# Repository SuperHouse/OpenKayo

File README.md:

# OpenKayo Kayo-A4 GCode Adapter

Connects to the serial interface of a Kayo-A4 pick-and-place
machine, and provides a USB interface with an onboard GCode 
interpreter that translates messages into the format necessary 
for the Kayo's motion controller.

This allows Kayo machines to be controlled using [OpenPnP](https://openpnp.org/).

## Hardware Requirements

You will need a computer running OpenPnP, with sufficient USB ports 
to handle the connections to the controller, cameras, etc. This 
is a normal OpenPnP requirement so check the OpenPnP docs for 
details.

The hardware adapter portion of the project can minimally be built with an
ESP8266-based dev board such as a Wemos D1 Mini and some cables.

A dedicated ESP32-S3 hardware design is provided, which includes
additional features such as a CAN bus interface to integrate with other
devices on the production line.

**Adapter Board Features**

 * USB-C socket for connection to host computer running OpenPnP
 * ESP32-S3 MCU
 * 3-way 3.81mm screw socket for connection to Kayo serial cable
 * Onboard USB hub with 2 spare ports exposed
 * RGB LED for status display
 * Connections for external RGB LED strip for traffic-light status display etc
 * 128x32 OLED
 * Piezo for alarms
 * CAN bus interface with optional CAN termination
 * Can be powered via USB if only a serial connection + USB is required
 * Can be powered at 12V via screw terminals to pass power on to CAN bus
 * Can be powered at 12V via CAN bus if another device on the bus is powered

## Serial Connection

Kayo machines are supplied with a Windows PC running their proprietary 
control software, which is connected to a motion 
controller mounted inside the chassis via a serial connection. The
serial port is connected using a 3-way 3.81mm pitch pluggable screw 
terminal, which includes signal GND, TX, and RX:

 * Logic voltage: 3.3V
 * 115200 8N1

## Axis Configuration

The protocol converter uses the axes listed below. OpenPnP needs to be 
configured to use these same axes.

 * X: horizontal left/right
 * Y: horizontal forward/back
 * Z: virtual vertical axis for top camera, which doesn't physically move vertically
 * A, B, C, D: rotational axes for nozzles 1-4
 * I, J, K, L: z (vertical) axes for nozzles 1-4

Kayo "home" is in the top right corner at coordinates "0,0", so the 
working area is negative coordinates relative to that. That may sound 
confusing at first but it works out quite nicely in practice. For example, 
a typical board origin when clamped on the conveyor could be at something 
like "-155, -453".

Nozzles are at a 0 position when fully retracted (raised) and typically 
descend to approximately -9.8mm to -10.1mm to touch the surface of a clamped 
PCB or feeder pickup location.

## Supported G-Codes

### Basic movement

| Code             | Meaning                                                                                              |
|------------------|------------------------------------------------------------------------------------------------------|
| G28              | Reset and home                                                                                       |
| G0 X*pos* Y*pos* | Move X & Y to the defined absolute position in mm, eg: "G0 X-23.4 Y-18"                              |
| G0 I*pos*        | Move specified nozzle vertically to absolute position in mm, eg: "G0 I-7.6" to send nozzle 1 to -7.6mm (I=n1, J=n2, K=n3, L=n4) |       
| G0 A*pos*        | Rotate specified nozzle to an absolute angle in degrees, eg: "G0 A48" to send nozzle 1 to an angle of 48 degrees (A=n1, B=n2, C=n3, D=n4)      |

**Note:** the Kayo motion controller has an interlock on X/Y movement with Z 
axis displacement. You CANNOT move the machine in X or Y axis while holding 
a nozzle partly extended. It handles this by automatically retracting all 
nozzles whenever it gets an X/Y movement command.

This means that you can't use advanced motion planning in OpenPnP, and you 
also can't assume that you know the Z axis position of any nozzle. If you 
move the head in X/Y, all Z axes will be immediately zeroed with no warning.

### Vac / Blow
| Code             | Meaning                                                                                              |
|------------------|------------------------------------------------------------------------------------------------------|
| M2 N*noz*        | Close vac and open blow on specified nozzle, eg: "M2 N2"                                             |
| M3               | Close vac and blow on all nozzles                                                                    |
| M4 N*noz*        | Open blow on selected nozzle, eg: "M4 N3"                                                            |
| M5 N*noz*        | Close blow on selected nozzle, eg: "M5 N2"                                                           |
| M6 N*noz*        | Open vac on selected nozzle, eg: "M6 N1"                                                             |
| M7 N*noz*        | Close vac on selected nozzle, eg: "M7 N1"                                                            |

### Conveyor Belt
| Code             | Meaning                                                                                              |
|------------------|------------------------------------------------------------------------------------------------------|
| M2               | Reset conveyor                                                                                       |
| M21 N*width*     | Adjust conveyor to specified width + configured margin, eg: "M21 N93.4"                              |
| M22              | Ingest a PCB and clamp it in position                                                                |
| M23              | Unclamp PCB and move it to the exit location                                                         |
| M24              | Start conveyor                                                                                       |
| M25              | Stop conveyor and drop pin                                                                           |
| M26              | Engages the stop pin                                                                                 |
| M27              | Clamp a PCB on the conveyor                                                                          |

### Lights
| Code              | Meaning                                                                                             |
|-------------------|-----------------------------------------------------------------------------------------------------|
| M30               | Turn off camera lights                                                                              |
| M31 S*brightness* | Turn on fast camera light at specified brightness %, eg: "M31 S15"                                 |
| M32 S*brightness* | Turn on precision camera light at specified brightness %, eg: "M32 S46"                             |

### Status
| Code             | Meaning                                                                                              |
|------------------|------------------------------------------------------------------------------------------------------|
| M114             | Report position                                                                                      |
| M115             | Report firmware type and version                                                                     |

### Feeders
| Code             | Meaning                                                                                              |
|------------------|------------------------------------------------------------------------------------------------------|
| M600 N*feeder*   | Open specified feeder, eg: "M600 N12"                                                                |
| M601             | Close feeders (no need to specify)                                                                   |

**Note:** The Kayo motion controller only ever allows a single feeder to be open 
at a time. If you have one feeder open and then send an open command for a different 
feeder, the first one will be closed automatically.

There is no command to close a specific feeder. M601 closes whatever was last opened.

### Diagnostic
| Code               | Meaning                                                                                            |
|--------------------|----------------------------------------------------------------------------------------------------|
|M99 N*noz* S*steps* | Send microsteps to specified nozzle rotation stepper, eg: "M99 N1 S1234"                           |

## Camera Modifications

### Bottom Cameras

I have been unable to connect the 5 factory bottom cameras (1 x precision 
camera and a 4-way high-speed camera array) to OpenPnP on either 
Ubuntu or MacOS. You may have more success on Windows: please let me know!

On my machines I have unscrewed the 4-way camera array and tucked it away 
under the feeder manifold, and also removed the precision camera. I replaced 
that with an ELP Mini 720p OV9712 USB industrial camera with a 6mm lens, 
using a 3D-printed camera mount and a lens spacer to change the focal length.

This particular camera is very commonly used for OpenPnP so it's a 
well-known and well-supported device.

**1. Remove light bracket and the original camera:**

**2. 3D-print mounting plate and lens spacer:**

**3. Remove lens from ELP camera:**

**4. Reattach lens with 6mm M2 bolts with spacer:**

**5. Attach mounting plate with M3 bolts:**

**6. Pass cable through mounting plate and screw camera on with 2mm self tappers:**

Finally, reinstall the light bracket and then do the usual focus and 
camera calibration process in OpenPnP.

### Top Camera

The top camera has an analog output. I connected it to an analog-to-HDMI 
converter, which then goes to a cheap HDMI-to-USB converter so that it 
appears as a webcam under Linux and can be accessed by OpenPnP.

## Discard Tray

You can use the original discard tray behind the PCB area, but with 
the 4-camera array removed there is an ideal location for a discard 
tray right behind the camera location. This allows a very short movement 
to the tray if the vision pipeline rejects the parts.

I have designed a discard tray holder that has a 1x2 Gridfinity mount 
in the base, and holes to attach it to the T-slot front rail using 
T-nuts and M3 bolts:

You can use a regular 1x2 Gridfinity tray. I've included a design for 
a 1x1 tray with the height set to match the mounting rail. OpenPnP 
currently only supports a single discard location, but support for 
multiple trays is in development:

## Kayo Protocol

The control protocol for the Kayo motion controller uses 8-byte 
messages in both directions, with no terminator. Message boundaries 
are discovered by watching for a leading character, tracking the 
number of bytes received, and timing out as a fallback to handle 
incomplete messages or errors.

The protocol is embodied in the source code. Docs to be added here 
later.

## Hardware

The "Hardware" directory contains the PCB design as an EAGLE project. 
This can be imported into KiCAD, or opened natively using Fusion360.

## Firmware

The "Firmware" directory contains example firmware as an Arduino
project. The full Arduino IDE board settings are in the header comment
of `OpenKayo.ino`.

**Important:** set Tools -> USB Mode to "USB-OTG (TinyUSB)", not
"Hardware CDC and JTAG". In Hardware CDC mode (tested with esp32 core
2.0.7), a reply whose last USB packet is exactly 64 bytes is held by
Linux hosts until the board sends more data. OpenPnP then times out
waiting for "ok", and its command confirmations get out of step.

The firmware sends exactly one response for each G-code line: "ok" when
the command has finished, or a single line starting with "ERR:" if it
failed. A command fails if the Kayo doesn't reply within the timeouts set
in `config.h`: 5 seconds for most commands, and 60 seconds for homing and
conveyor commands. In OpenPnP's GcodeDriver settings:

 * "Command Error Regex" should match `^ERR:.*`, so that a failed command
   stops the job straight away.
 * "Command Timeout [ms]" must be longer than the firmware's longest
   timeout, for example 65000. If OpenPnP gives up first, its command
   confirmations get out of step.

## Credits

 * Jonathan Oxer <jon@oxer.com.au>

Heavily inspired by Glen English's Python-based UI for the Kayo, in
particular his work decoding the message format used by the factory
software.

## License

Copyright 2022-2025 SuperHouse Automation Pty Ltd  www.superhouse.tv  

The hardware portion of this project is licensed under the TAPR Open
Hardware License (www.tapr.org/OHL). The "license" folder within this
repository contains a copy of this license in plain text format.

The software portion of this project is licensed under the Simplified
BSD License. The "licence" folder within this project contains a
copy of this license in plain text format.

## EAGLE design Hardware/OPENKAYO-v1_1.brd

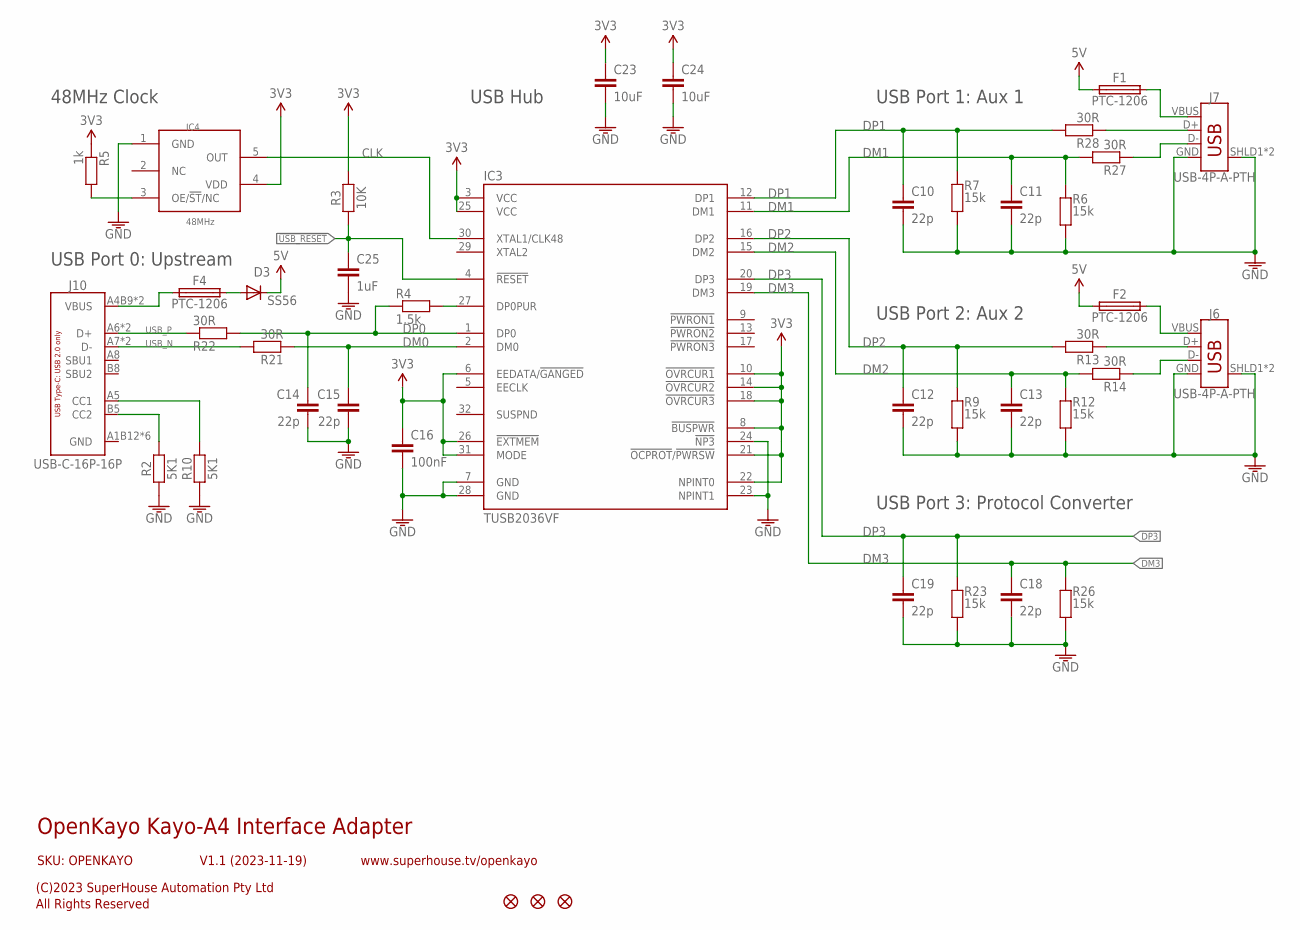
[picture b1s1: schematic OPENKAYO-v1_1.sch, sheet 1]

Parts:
C10, C11, C12, C13, C14, C15, C18, C19: 22p; C0603
C16: 100nF; C0603
C23, C24: 10uF; C0805
C25: 1uF; C0603
D3: SS56; SMA-DIODE
F1, F2, F4: PTC-1206; 1206
FID1, FID2, FID3: FIDUCIAL1X2.5; FIDUCIAL-1X2.5
IC3: TUSB2036VF; PQFP-G32
IC4: 48MHz; SOT-23-5
J6, J7: USB-4P-A-PTH; USB-A-PTH
J10: USB-C-16P-16P; USB-C-16P
R2, R10: 5K1; R0603
R3: 10K; R0603
R4: 1.5k; R0603
R5: 1k; R0603
R6, R7, R9, R12, R23, R26: 15k; R0603
R13, R14, R21, R22, R27, R28: 30R; R0603

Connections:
3.3V: C16.1, C23.1, C24.1, IC3.3 (VCC), IC3.6 (EEDATA/!GANGED), IC3.8 (!BUSPWR), IC3.10 (!OVRCUR1), IC3.14 (!OVRCUR2), IC3.18 (!OVRCUR3), IC3.21 (!OCPROT!/!PWRSW!), IC3.22 (NPINT0), IC3.25 (VCC), IC3.26 (!EXTMEM), IC3.31 (MODE), IC4.4 (VDD), R3.2, R5.1; also elsewhere on the board
5V: D3.C, F1.1, F2.1; also elsewhere on the board
!USB_RESET: C25.1, IC3.4 (!RESET), R3.1
CLK: IC3.30 (XTAL1/CLK48), IC4.5 (OUT)
DM0: C15.1, IC3.2 (DM0), R21.2
DM1: C11.1, IC3.11 (DM1), R6.1, R27.2
DM2: C13.1, IC3.15 (DM2), R12.1, R14.2
DM3: C18.1, IC3.19 (DM3), R26.1; also elsewhere on the board
DP0: C14.1, IC3.1 (DP0), R4.1, R22.2
DP1: C10.1, IC3.12 (DP1), R7.1, R28.2
DP2: C12.1, IC3.16 (DP2), R9.1, R13.2
DP3: C19.1, IC3.20 (DP3), R23.1; also elsewhere on the board
GND: C10.2, C11.2, C12.2, C13.2, C14.2, C15.2, C16.2, C18.2, C19.2, C23.2, C24.2, C25.2, IC3.7 (GND), IC3.23 (NPINT1), IC3.24 (!NP3), IC3.28 (GND), IC4.1 (GND), J6.GND, J6.SHLD1 (SHIELD), J6.SHLD2 (SHIELD), J7.GND, J7.SHLD1 (SHIELD), J7.SHLD2 (SHIELD), J10.A1B12 (GND), J10.A12B1 (GND), J10.FIX1 (GND), J10.FIX2 (GND), J10.FIX3 (GND), J10.FIX4 (GND), R2.1, R6.2, R7.2, R9.2, R10.1, R12.2, R23.2, R26.2; also elsewhere on the board
unnamed: IC3.27 (DP0PUR), R4.2
unnamed: IC4.3 (OE/!ST!/NC), R5.2
unnamed: F1.2, J7.VBUS
unnamed: F2.2, J6.VBUS
unnamed: J10.B5 (CC2), R2.2
unnamed: J10.A5 (CC1), R10.2
unnamed: J6.D+, R13.1
unnamed: J6.D-, R14.1
unnamed: J7.D+, R28.1
unnamed: J7.D-, R27.1
unnamed: F4.1, J10.A4B9 (VBUS), J10.A9B4 (VBUS)
unnamed: D3.A, F4.2
USB_N: J10.A7 (D-), J10.B7 (D-), R21.1
USB_P: J10.A6 (D+), J10.B6 (D+), R22.1

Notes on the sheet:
OpenKayo Kayo-A4 Interface Adapter
V1.1 (2023-11-19)
SKU: OPENKAYO
(C)2023 SuperHouse Automation Pty Ltd
All Rights Reserved
www.superhouse.tv/openkayo
USB Port 1: Aux 1
USB Port 2: Aux 2
USB Port 3: Protocol Converter
USB Hub
USB Port 0: Upstream
48MHz Clock

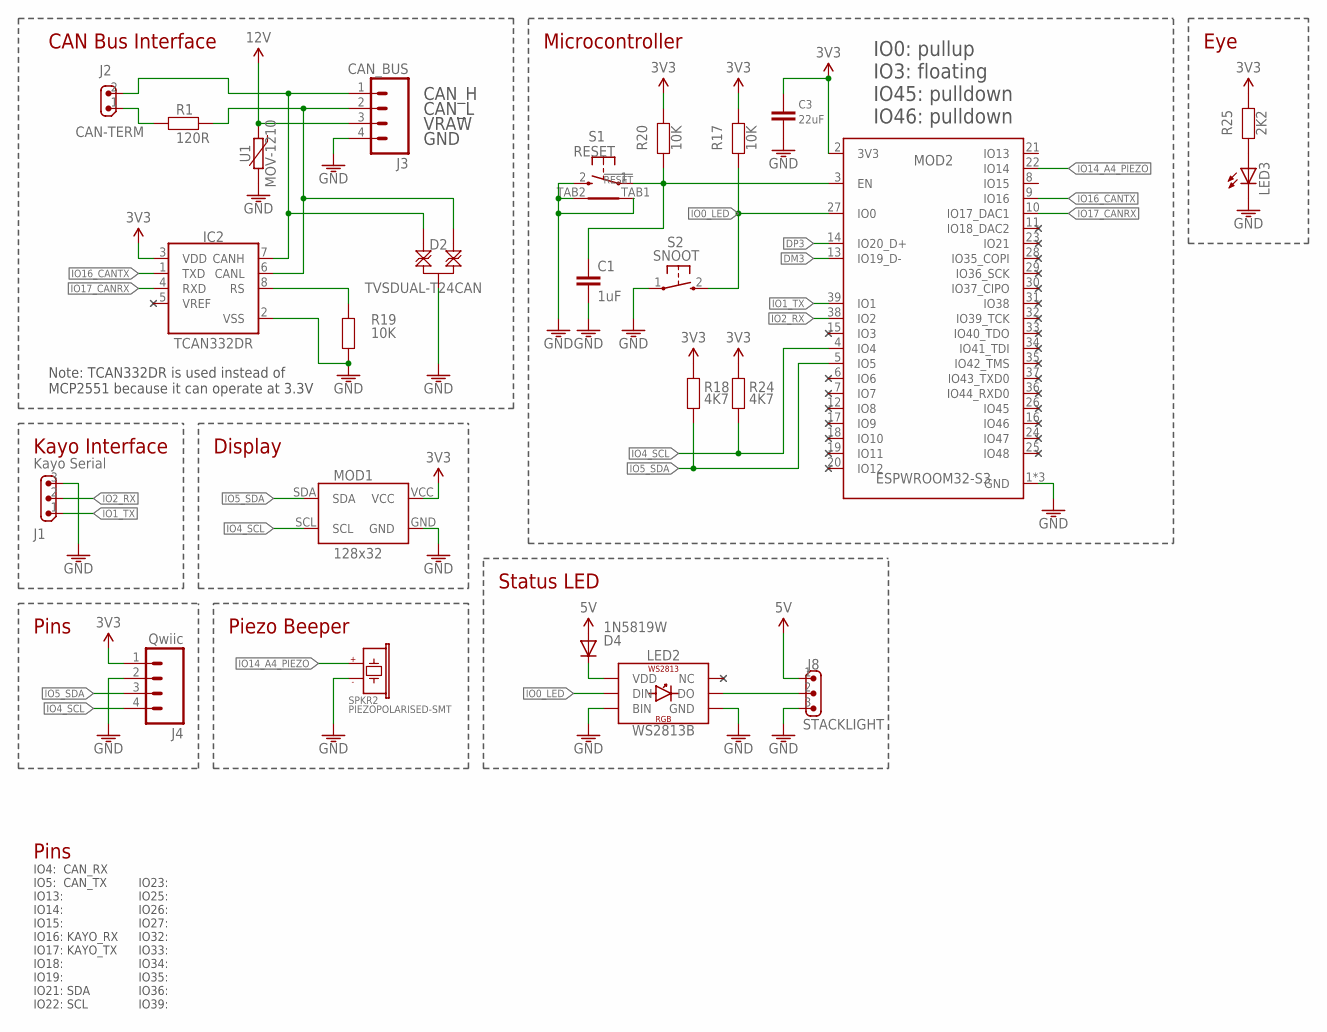
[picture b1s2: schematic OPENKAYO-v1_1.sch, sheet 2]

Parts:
C1: 1uF; C0603
C3: 22uF; C0805
D2: TVSDUAL-T24CAN; SOT23-3
D4: 1N5819W; SOD-123
IC2: TCAN332DR; SOIC8
J1: Kayo Serial; SCREWTERMINAL-3.81MM-HOR-3
J2: CAN-TERM; 1X02-P-JUMP-Y
J3: CAN_BUS; SCREWTERMINAL-3.81MM-HOR-4
J4: Qwiic; JST-SM4B-SH
J8: STACKLIGHT; 1X03
LED2: WS2813B; WS2813
LED3: LED0603; LED-0603
MOD1: 128x32; OLED-128X32-0.91-HEADER
MOD2: ESPWROOM32-S3
R1: 120R; R2010
R17, R19, R20: 10K; R0603
R18, R24: 4K7; R0603
R25: 2K2; R0603
S1: RESET; TYCO-FSMRAJ
S2: SNOOT; TACTILE_SMT_3X4X2
SPKR2: PIEZOPOLARISED-SMT; PIEZO-9.6X9.6-SMT
U1: MOV-1210; 1210

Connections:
3.3V: C3.1, IC2.3 (VDD), J4.1, MOD1.VCC, MOD2.2 (3V3), R17.1, R18.1, R20.1, R24.1, R25.1; also elsewhere on the board
5V: D4.2 (A), J8.1; also elsewhere on the board
12V: J3.3, U1.2; also elsewhere on the board
!RESET: C1.1, MOD2.3 (EN), R20.2, S1.1
CAN_H: D2.2, IC2.7 (CANH), J2.2, J3.1
CAN_L: D2.1, IC2.6 (CANL), J3.2, R1.2
DM3: MOD2.13 (IO19_D-); also elsewhere on the board
DP3: MOD2.14 (IO20_D+); also elsewhere on the board
GND: C1.2, C3.2, D2.3, IC2.2 (VSS), J1.3, J3.4, J4.2, J8.3, LED2.5 (GND), LED2.6 (BIN), LED3.C, MOD1.GND, MOD2.1 (GND), MOD2.40 (GND), MOD2.41 (GND), R19.1, S1.2, S1.TAB1, S1.TAB2, S2.1, SPKR2.2 (-), U1.1; also elsewhere on the board
IO0_LED: LED2.4 (DIN), MOD2.27 (IO0), R17.2, S2.2 (S)
IO1_TX: J1.1, MOD2.39 (IO1)
IO2_RX: J1.2, MOD2.38 (IO2)
IO4_SCL: J4.4, MOD1.SCL, MOD2.4 (IO4), R24.2
IO5_SDA: J4.3, MOD1.SDA, MOD2.5 (IO5), R18.2
IO14_A4_PIEZO: MOD2.22 (IO14), SPKR2.1 (+)
IO16_CANTX: IC2.1 (TXD), MOD2.9 (IO16)
IO17_CANRX: IC2.4 (RXD), MOD2.10 (IO17_DAC1)
IO46: MOD2.16 (IO46)
unnamed: IC2.8 (RS), R19.2
unnamed: LED3.A, R25.2
unnamed: J2.1, R1.1
unnamed: D4.1 (C), LED2.2 (VDD)
unnamed: J8.2, LED2.3 (DO)
NC: LED2.1 (NC)

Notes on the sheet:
CAN Bus Interface
Note: TCAN332DR is used instead of MCP2551 because it can operate at 3.3V
CAN_H
CAN_L
GND
VRAW
Kayo Interface
Piezo Beeper
IO4: CAN_RX IO5: CAN_TX IO13: IO14: IO15: IO16: KAYO_RX IO17: KAYO_TX IO18: IO19: IO21: SDA IO22: SCL
Pins
IO23: IO25: IO26: IO27: IO32: IO33: IO34: IO35: IO36: IO39:
Microcontroller
Display
Status LED
IO0: pullup IO3: floating IO45: pulldown IO46: pulldown
Eye

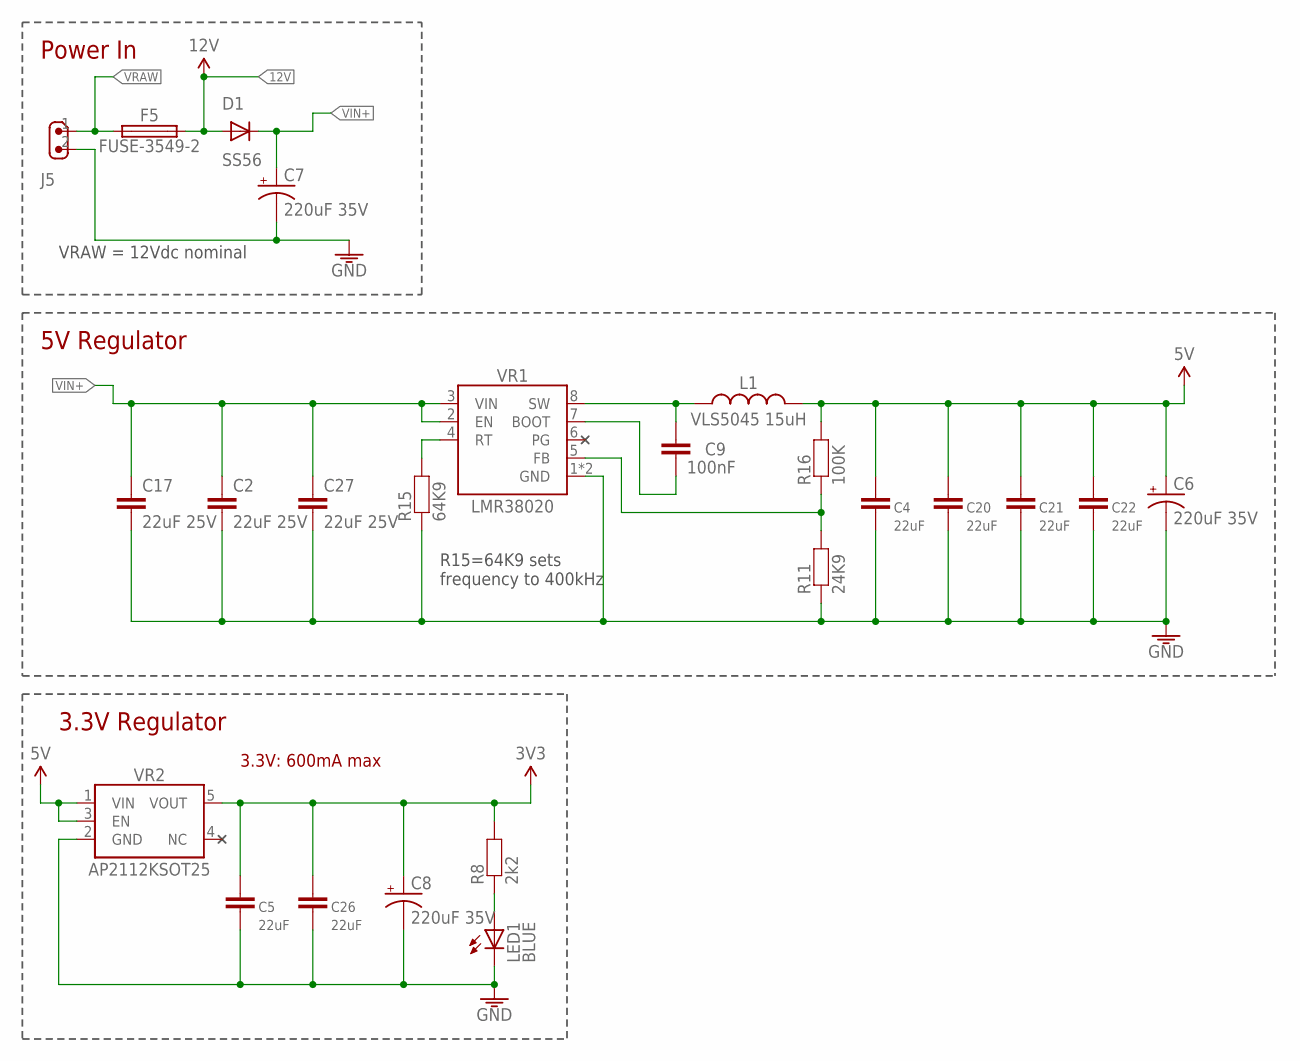
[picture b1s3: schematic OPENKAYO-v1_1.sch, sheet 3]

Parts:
C2, C17, C27: 22uF 25V; C0805
C4, C5, C20, C21, C22, C26: 22uF; C0805
C6, C7, C8: 220uF 35V; PANASONIC_G
C9: 100nF; C0603
D1: SS56; SMA-DIODE
F5: FUSE-3549-2; KS-3549-2
J5: M02-SCREW-3.81MM-HOR; SCREWTERMINAL-3.81MM-HOR-2
L1: VLS5045 15uH; INDUCTOR-5045
LED1: BLUE; LED-0603
R8: 2k2; R0603
R11: 24K9; R0603
R15: 64K9; R0603
R16: 100K; R0603
VR1: LMR38020; HSOIC8
VR2: AP2112KSOT25; SOT23-5

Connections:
3.3V: C5.1, C8.+, C26.1, R8.2, VR2.5 (VOUT); also elsewhere on the board
5V: C4.1, C6.+, C20.1, C21.1, C22.1, L1.2, R16.2, VR2.1 (VIN), VR2.3 (EN); also elsewhere on the board
12V: D1.A, F5.3 (2), F5.4 (2); also elsewhere on the board
GND: C2.2, C4.2, C5.2, C6.-, C7.-, C8.-, C17.2, C20.2, C21.2, C22.2, C26.2, C27.2, J5.2, LED1.C, R11.1, R15.1, VR1.1 (GND), VR1.TGND (GND), VR2.2 (GND); also elsewhere on the board
unnamed: C9.1, L1.1, VR1.8 (SW)
unnamed: R15.2, VR1.4 (RT)
unnamed: R11.2, R16.1, VR1.5 (FB)
unnamed: C9.2, VR1.7 (BOOT)
unnamed: LED1.A, R8.1
PG: VR1.6 (PG)
VIN+: C2.1, C7.+, C17.1, C27.1, D1.C, VR1.2 (EN), VR1.3 (VIN)
VRAW: F5.1, F5.2 (1), J5.1

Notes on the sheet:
3.3V: 600mA max
VRAW = 12Vdc nominal
5V Regulator
3.3V Regulator
Power In
R15=64K9 sets frequency to 400kHz

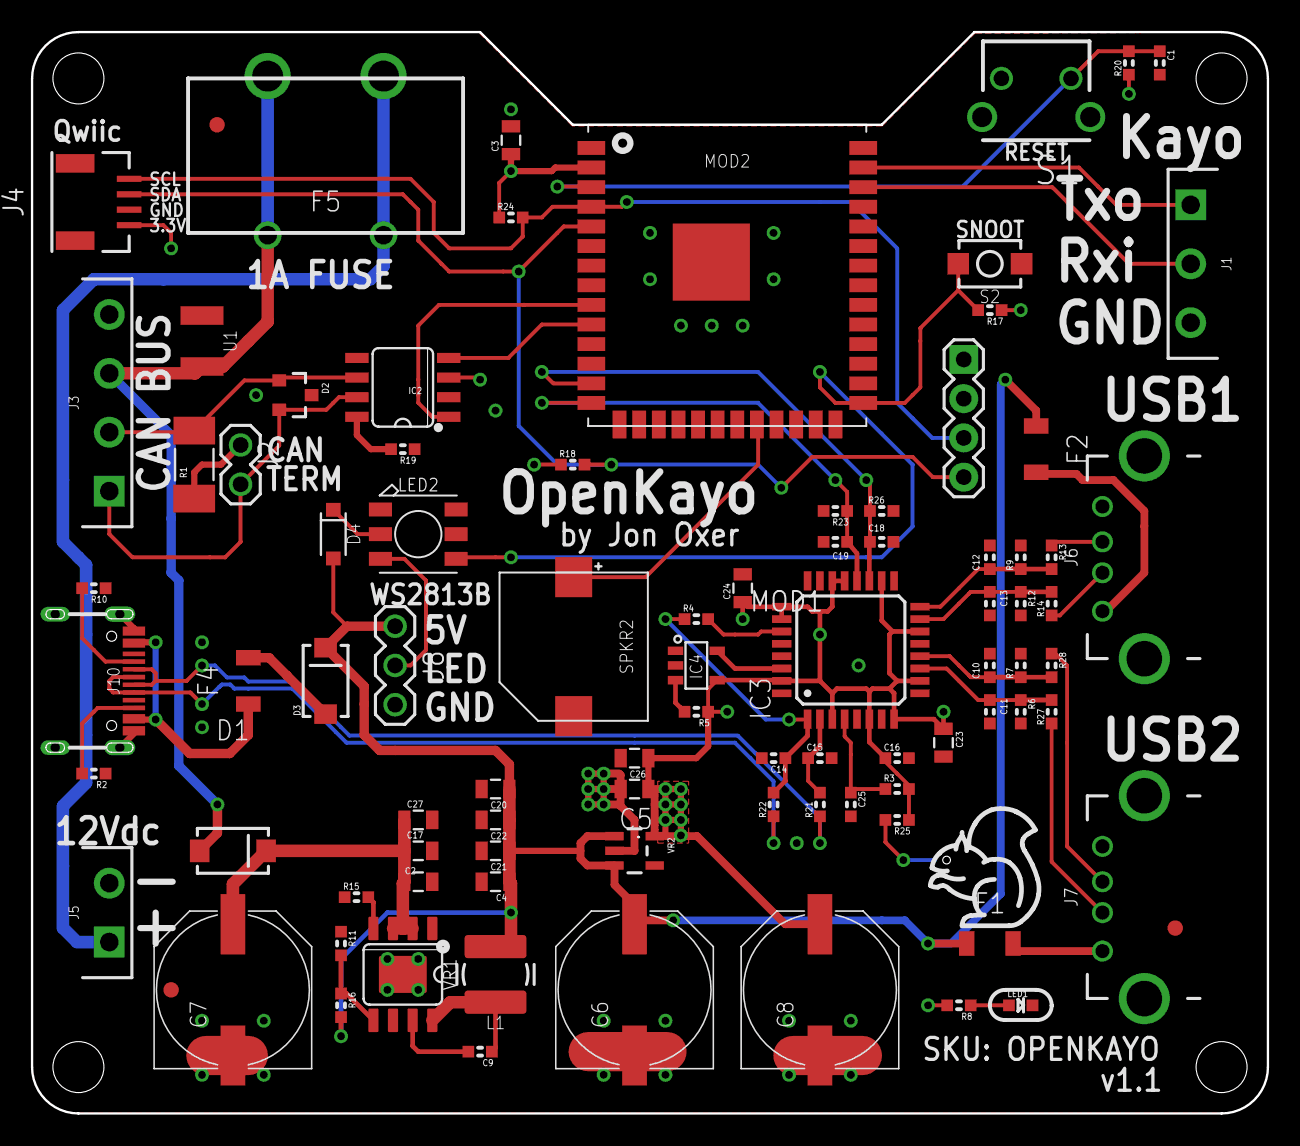
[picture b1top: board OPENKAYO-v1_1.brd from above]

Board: 4 copper layers, 80.0 x 70.0 mm, 90 parts (1 on the bottom side), 51 nets.

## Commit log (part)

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2022-09-13 Initial import of project in progress.
2022-09-14 Added early test using Python script.
2022-12-29 Added config option to enable message debugging. Track both requested X/Y position and reported position. Added ability to require exact match on expected response messages. Added config option to ap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
2022-12-30 Expanded axes to allow control of 4 nozzles via GCode. Special-case on moving to 0 on Z axes to allow true full retraction.
2022-12-30 Added message formats from Glen's Python driver for reference.
2022-12-30 Cleaned up README.
2022-12-30 Hide debugging messages unless debugging is turned on.
2023-07-21 Fixed handling of blowoff by controlling suppliment valve.
2023-07-21 Removed experimental code for handling multiple feeder advance distances.
2023-07-21 Turned on require-homing in default config and clarified other config values.
2023-12-16 Pin changes to support dedicated OpenKayo hardware.
2025-11-25 Firmware conversion to S3, with CAN bus currently partly broken.
2025-11-25 Added hardware design files and updated README.
2025-11-25 Fixed dimensions of LCD
2025-11-25 Expanded README with documentation of G-Codes, axes, and camera connections.
2025-11-25 Added hardware features to README
2025-11-25 More notes about axes and coordinates.
2025-11-25 Typos
2025-11-26 Added printable parts to assist with conversion
2025-11-30 Added images and instructions for mounting ELP camera
2025-11-30 Added pics and description of fitting discard trays
